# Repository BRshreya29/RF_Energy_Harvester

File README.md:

# RF Energy Harvester – 2.4 GHz

This repository contains the complete design, fabrication, and testing files for a **2.4 GHz RF Energy Harvester**, including antenna design, rectifier circuit design, CST simulations, KiCAD PCB layouts, fabrication outputs, and VNA measurement results.

The harvester is designed for low-power IoT applications and captures RF energy in the 2.4 GHz ISM band.  
The project includes **antenna simulation + PCB**, **rectifier circuit + PCB**, and full hardware testing.

---

## 1. Antenna Design (CST Studio)

The antenna was designed and optimized in **CST Studio** for the 2.45 GHz ISM band.

### Key Features  
- Designed for 2.4–2.5 GHz bandwidth  
- Simulated S11 < –22 dB at resonance  
- Fabricated as a **double-layer PCB**  
- Measured using **R60 Vector Network Analyzer**

### Antenna Images  
#### CST Antenna Model  

#### CST S11 Simulation  

#### Fabricated Antenna  

#### PCB Layout  

#### VNA Measurement (Hardware S11)  
Achieved a **return loss of –22.209 dB at 2.48 GHz**, which is excellent and closely matches simulations.

---

## 2. Antenna PCB Files (KiCAD)

The antenna PCB was fully designed in **KiCAD**, fabricated in the lab, and assembled manually.

### PCB Highlights  
- **Double-layer PCB** for RF stability  
- **Vias added** for grounding and performance  
- **Custom SMA connector footprint** created because KiCAD did not have the required part  
- SMA footprint file:
```
Antenna/Antenna_PCB_files/Library/SMAmale.kicad_mod
```

### PCB Files  
```
Antenna/Antenna_PCB_files/KiCAD pcb files
Antenna/Antenna_PCB_files/antenna_gerber_files.zip
Antenna/Antenna_PCB_files/Library/SMAmale.kicad_mod
```

---

## 3. Rectifier Circuit (ADS + KiCAD)

The rectifier circuit uses a multi-stage RF-to-DC rectification approach.  
The circuit was simulated in **ADS**, then designed as a **double-layer PCB** in KiCAD.

### Circuit Images  
#### Schematic  

#### PCB Layout  

#### Fabricated Rectifier Board  

### PCB Files  
```
Circuit_board_PCB_files/KiCAD pcb files
Circuit_board_PCB_files/gerber files (2).zip
Circuit_board_PCB_files/Library/SMA.kicad_mod
```

### PCB Highlights  
- Designed in **KiCAD**  
- **RF-friendly routing** with short traces  
- **Ground vias stitched** for stability  
- **Custom SMA connector footprint** added:
```
Circuit_board_PCB_files/Library/SMA.kicad_mod
```

---

## 4. Repository Structure

```
RF_Energy_Harvester_2.4GHz/
│
├── README.md
│
├── Antenna/
│   ├── Antenna_Images/
│   │   ├── Multiple_images
│   ├── Antenna_PCB_files/
│   │   ├── KiCAD_PCB_files
|   |   ├── gerber_files.zip
│   │   └── Library/SMAmale.kicad_mod
│   └── CST_Files/antenna3.cst
│
├── Cicuit_board_images/
│   ├── Circuit_PCB_layout.png
│   ├── Circuit_schematic.png
│   └── Fabricated_circuit.jpg
│
├── Circuit_board_PCB_files/
│   │   ├── KiCAD_PCB_files
│   ├── gerber files (2).zip
│   └── Library/SMA.kicad_mod
│
└── RF_Energy_Harvester_Documentation.pdf
```

---

## 5. Documentation

Complete design report, analysis, S11 results, and rectifier circuit details:

```
RF_Energy_Harvester_Documentation.pdf
```

---

## Summary

This repository contains:

- CST antenna simulation  
- KiCAD PCB design for antenna and rectifier  
- ADS circuit simulation  
- Fabricated double-layer PCBs  
- VNA-measured return loss of **–22.209 dB at 2.48 GHz**  
- Custom SMA footprints  
- Complete fabrication-ready Gerber files  

The project successfully demonstrates a working **2.4 GHz RF Energy Harvester** with close agreement between simulation and hardware of antenna only.

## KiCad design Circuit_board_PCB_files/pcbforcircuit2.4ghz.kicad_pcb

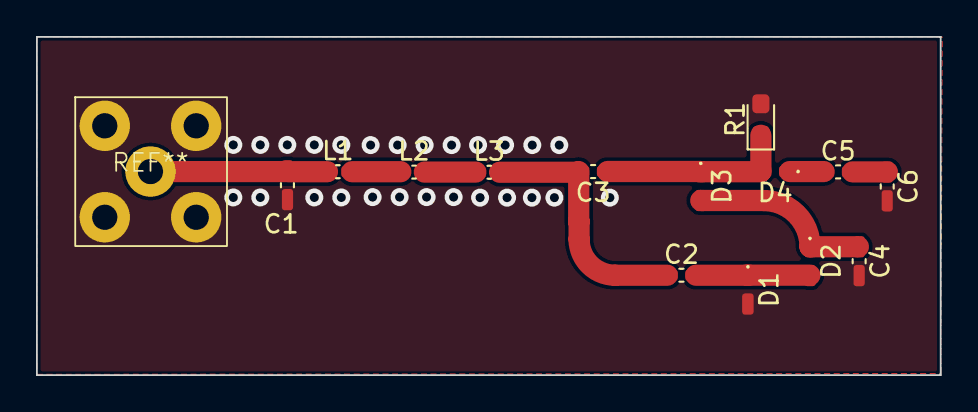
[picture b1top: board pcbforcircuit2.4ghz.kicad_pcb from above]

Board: 2 copper layers, 50.2 x 18.8 mm, 14 parts (0 on the bottom side), 7 nets.

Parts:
C1: 2pF; C_0402_1005Metric_Pad0.74x0.62mm_HandSolder
C2, C3, C4: 15pF; C_0402_1005Metric_Pad0.74x0.62mm_HandSolder
C5, C6: 10pF; C_0402_1005Metric_Pad0.74x0.62mm_HandSolder
D1, D2, D3, D4: D_Schottky; D_0402_1005Metric_Pad0.77x0.64mm_HandSolder
L1: 10nH; L_0402_1005Metric_Pad0.77x0.64mm_HandSolder
L2: 1.8nH; L_0402_1005Metric_Pad0.77x0.64mm_HandSolder
L3: 2.2nH; L_0402_1005Metric_Pad0.77x0.64mm_HandSolder
R1: 50k; D_0603_1608Metric_Pad1.05x0.95mm_HandSolder

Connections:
0: C1.2, C4.2, C6.2, D1.2 (A), R1.2
unnamed: C2.1, C3.2, L3.2
unnamed: C5.2, C6.1
unnamed: C2.2, C3.1, C4.1, D1.1 (K), D2.1 (K), D2.2 (A), D3.1 (K), D3.2 (A), D4.1 (K), D4.2 (A), R1.1
unnamed: C1.1, L1.1
unnamed: L1.2, L2.1
unnamed: L2.2, L3.1
